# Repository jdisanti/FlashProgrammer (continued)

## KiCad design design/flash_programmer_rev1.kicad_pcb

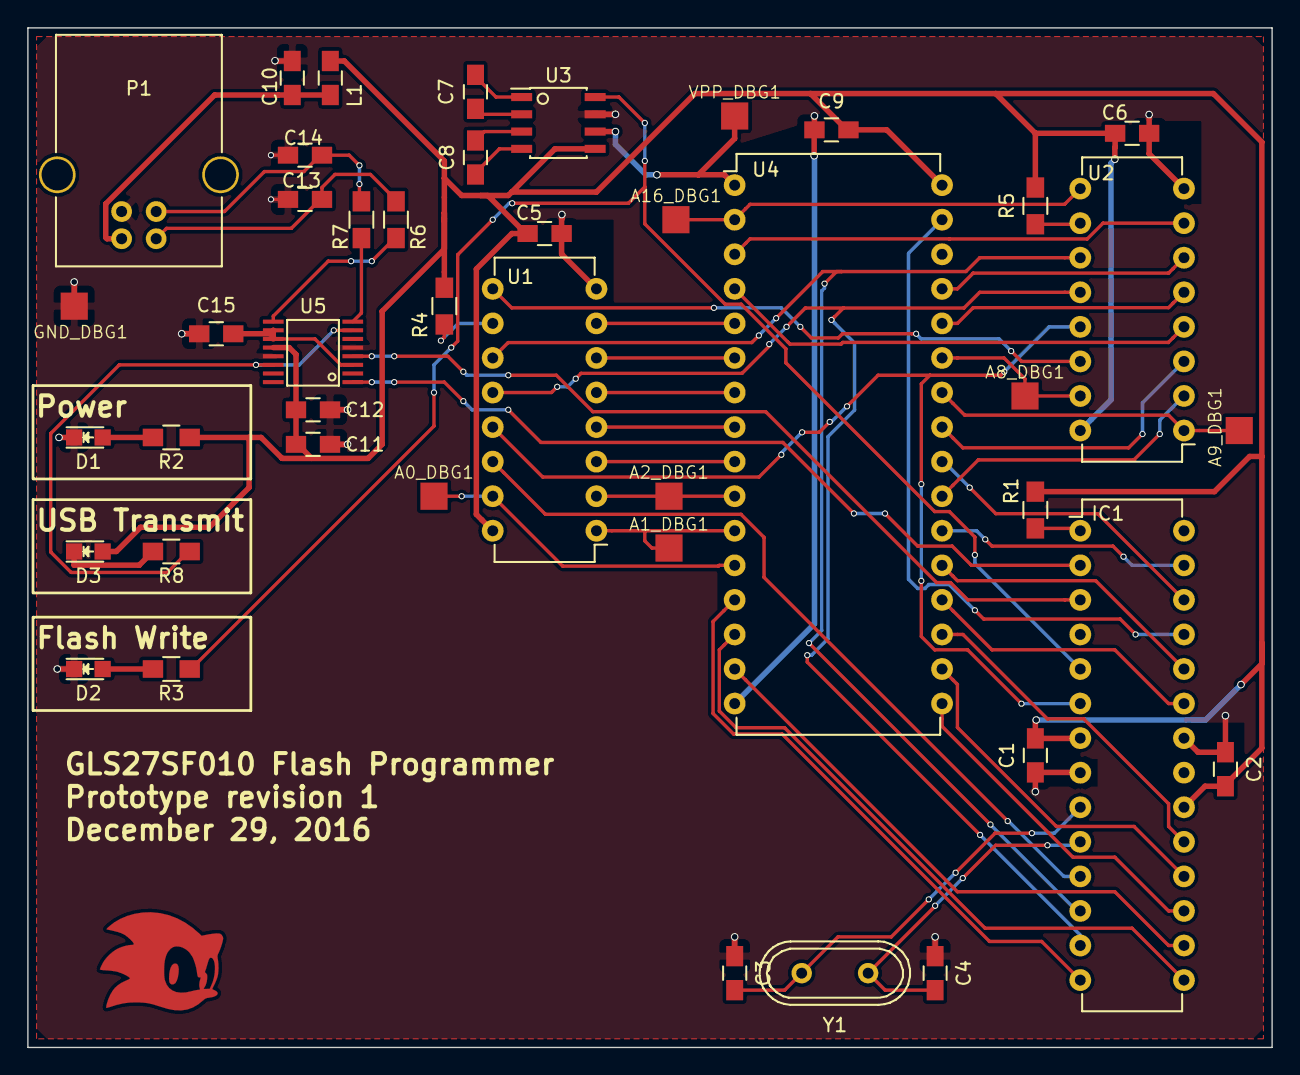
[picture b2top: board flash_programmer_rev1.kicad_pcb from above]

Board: 2 copper layers, 91.4 x 74.9 mm, 43 parts (0 on the bottom side), 58 nets.

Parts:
A0_DBG1, A1_DBG1, A2_DBG1, A8_DBG1, A9_DBG1, A16_DBG1: debug_pad; DBG_PAD
C1, C2, C5, C6, C9, C12, C15: 120nF; C_0805_HandSoldering
C3, C4: 22pF; C_0805_HandSoldering
C7, C8: 1uF; C_0805_HandSoldering
C10: 10nF; C_0805_HandSoldering
C11: 4.7uF; C_0805_HandSoldering
C13, C14: 47pF; C_0805_HandSoldering
D1, D2, D3: LED; LED_0805
GND_DBG1: debug_pad; DBG_PAD
IC1: ATMEGA328-P; DIP-28_W7.62mm
L1: Ferrite_Bead; C_0805_HandSoldering
P1: USB_B
R1, R4, R5: 10k; R_0805_HandSoldering
R2, R3, R8: 150; R_0805_HandSoldering
R6, R7: 27; R_0805_HandSoldering
U1, U2: 74HC595; DIP-16_W7.62mm
U3: MAX662A; SOIC-8_3.9x4.9mm_Pitch1.27mm
U4: GLS27SF010; DIP-32_W15.24mm
U5: FT230X; SSOP-16
VPP_DBG1: debug_pad; DBG_PAD
Y1: 16MHz; Crystal_HC49-U_Vertical

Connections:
/A0: A0_DBG1.1, U1.15, U4.12
/A1: A1_DBG1.1, U1.1, U4.11
/A2: A2_DBG1.1, U1.2, U4.10
/A3: U1.3, U4.9
/A4: U1.4, U4.8
/A5: U1.5, U4.7
/A6: U1.6, U4.6
/A7: U1.7, U4.5
/A8: A8_DBG1.1, U2.15, U4.27
/A9: A9_DBG1.1, U2.1, U4.26
/A10: U2.2, U4.23
/A11: U2.3, U4.25
/A12: U2.4, U4.4
/A13: U2.5, U4.28
/A14: U2.6, U4.29
/A15: U2.7, U4.3
/A16: A16_DBG1.1, U2.9, U4.2
/AOE: IC1.6, U1.13, U2.13
/CE#: IC1.27, U4.22
/D0: IC1.14, U4.13
/D1: IC1.15, U4.14
/D2: IC1.16, U4.15
/D3: IC1.17, U4.17
/D4: IC1.18, U4.18
/D5: IC1.19, U4.19
/D6: IC1.23, U4.20
/D7: IC1.24, U4.21
/Flash Programmer FTDI Circuit/USBDM: C13.1, P1.2, R6.2
/Flash Programmer FTDI Circuit/USBDP: C14.1, P1.3, R7.2
/Flash Programmer FTDI Circuit/VCCIO: C15.2, U5.3, U5.10, U5.11
/OE#: IC1.26, U4.24
/PGM#: IC1.25, U4.31
/RCK: IC1.13, U1.12, U2.12
/RXD: IC1.2, U5.1
/SCK: IC1.12, U1.11, U2.11
/SER: IC1.11, U1.14
/STU: IC1.5, R3.2, U3.8
/TXD: IC1.3, U5.4
/VPP: U3.6, U4.1, VPP_DBG1.1
GND: C1.1, C2.1, C3.1, C4.1, C5.1, C6.1, C9.1, C10.2, C11.2, C12.2, C13.2, C14.2, C15.1, D1.1, D2.1, GND_DBG1.1, IC1.8, IC1.22, P1.4, U1.8, U2.8, U3.7, U4.16, U5.5, U5.13
unnamed: C3.2, IC1.9, Y1.2
unnamed: C4.2, IC1.10, Y1.1
unnamed: C7.1, U3.1
unnamed: C7.2, U3.2
unnamed: C8.1, U3.4
unnamed: C8.2, U3.3
unnamed: C10.1, L1.2, P1.1
unnamed: D1.2, R2.1
unnamed: D2.2, R3.1
unnamed: D3.1, R8.1
unnamed: IC1.1, R1.2
unnamed: R4.1, U1.10
unnamed: R5.1, U2.10
unnamed: R6.1, U5.9
unnamed: R7.1, U5.8
unnamed: R8.2, U5.7, U5.14
unnamed: U1.9, U2.14
VCC: C1.2, C2.2, C5.2, C6.2, C9.2, C11.1, C12.1, D3.2, IC1.7, IC1.20, L1.1, R1.1, R2.2, R4.2, R5.2, U1.16, U2.16, U3.5, U4.32, U5.12

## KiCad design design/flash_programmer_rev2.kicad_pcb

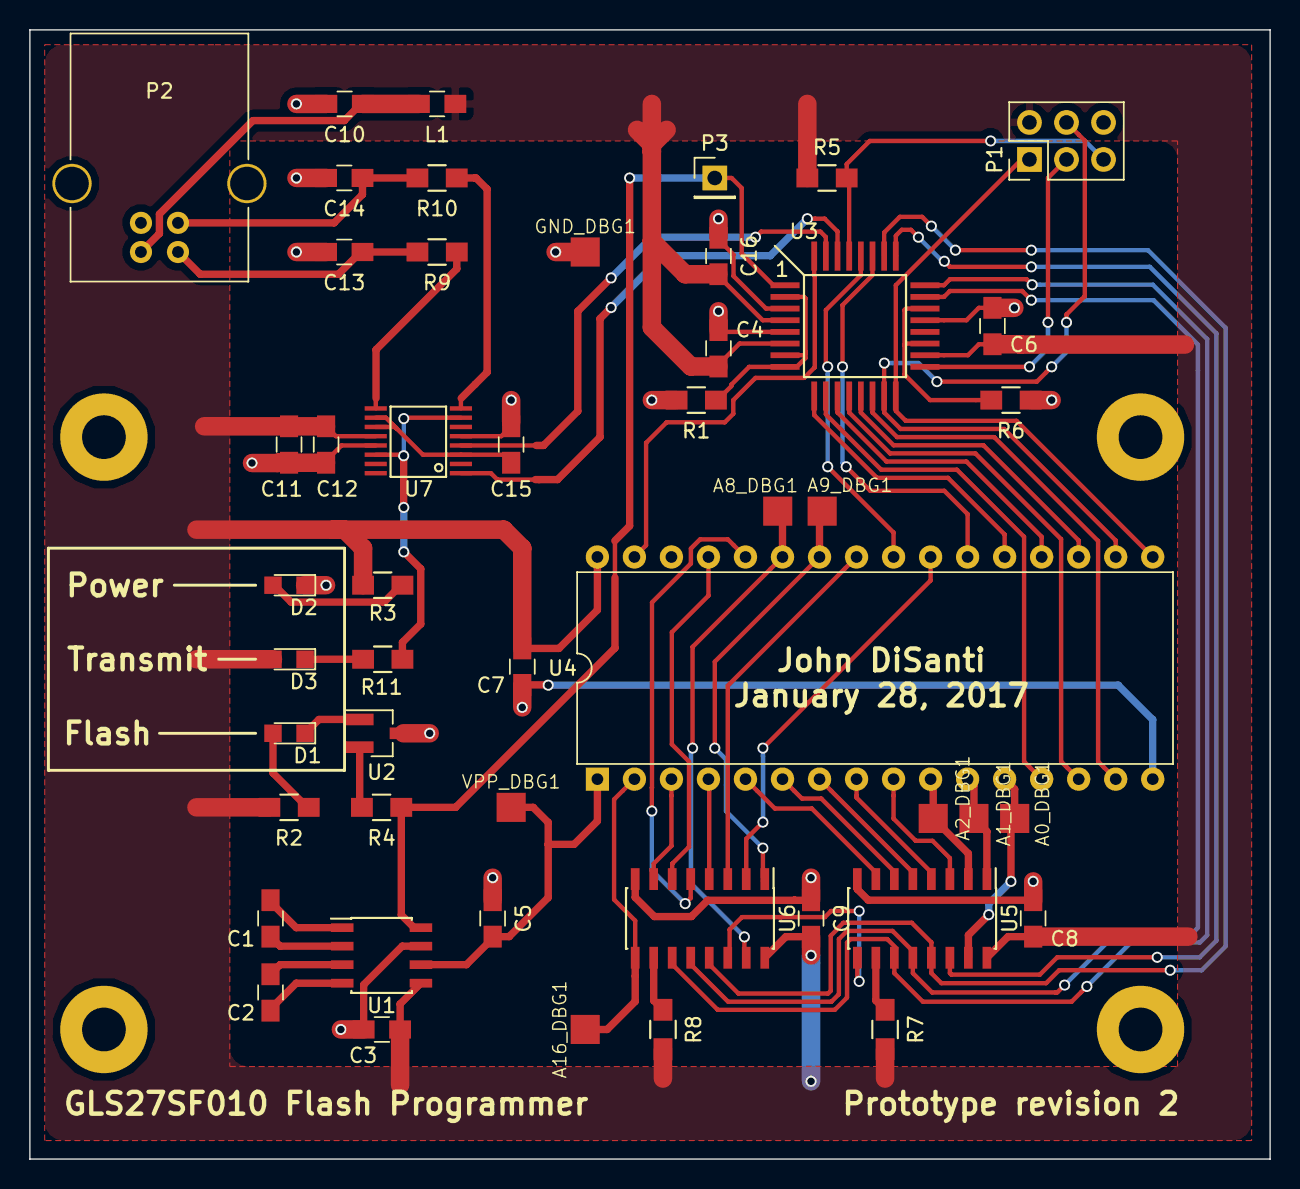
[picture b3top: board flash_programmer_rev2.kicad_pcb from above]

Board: 2 copper layers, 85.1 x 77.5 mm, 49 parts (0 on the bottom side), 61 nets.

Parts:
A0_DBG1, A1_DBG1, A2_DBG1, A8_DBG1, A9_DBG1, A16_DBG1: debug_pad; DBG_PAD
C1, C2: 22nF; C_0805_HandSoldering
C3, C5, C11: 4.7uF; C_0805_HandSoldering
C4, C6, C7, C8, C9, C12, C15, C16: 120nF; C_0805_HandSoldering
C10: 10nF; C_0805_HandSoldering
C13, C14: 47pF; C_0805_HandSoldering
D1, D2, D3: LED; LED_0805
GND_DBG1: debug_pad; DBG_PAD
L1: Ferrite_Bead; C_0805_HandSoldering
P1: ISP; Pin_Header_Straight_2x03_Pitch2.54mm
P2: USB_B
P3: STU_DBG1; Pin_Header_Straight_1x01_Pitch2.54mm
R1, R4, R5, R6, R7, R8: 10k; R_0805_HandSoldering
R2, R3, R11: 150; R_0805_HandSoldering
R9, R10: 27; R_0805_HandSoldering
U1: MAX662A; SOIC-8_3.9x4.9mm_Pitch1.27mm
U2: 2N3906; SOT-23_Handsoldering
U3: ATMEGA328P_TQFN; TQFP-32
U4: GLS27SF010; DIP-32_W15.24mm
U5, U6: 74HC595; SOIC-16_3.9x9.9mm_Pitch1.27mm
U7: FT230X; SSOP-16
VPP_DBG1: debug_pad; DBG_PAD

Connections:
/A0: A0_DBG1.1, U4.12, U5.15
/A1: A1_DBG1.1, U4.11, U5.1
/A2: A2_DBG1.1, U4.10, U5.2
/A3: U4.9, U5.3
/A4: U4.8, U5.4
/A5: U4.7, U5.5
/A6: U4.6, U5.6
/A7: U4.5, U5.7
/A8: A8_DBG1.1, U4.27, U6.15
/A9: A9_DBG1.1, U4.26, U6.1
/A10: U4.23, U6.2
/A11: U4.25, U6.3
/A12: U4.4, U6.4
/A13: U4.28, U6.5
/A14: U4.29, U6.6
/A15: U4.3, U6.7
/A16: A16_DBG1.1, U4.2, U6.9
/AOE: U3.26, U5.13, U6.13
/CE#: U3.27, U4.22
/D0: U3.10, U4.13
/D1: U3.12, U4.14
/D2: U3.14, U4.15
/D3: P1.1, U3.16, U4.17
/D4: P1.4, U3.15, U4.18
/D5: U3.13, U4.19
/D6: U3.11, U4.20
/D7: U3.9, U4.21
/Flash Programmer FTDI Circuit/USBDM: C13.1, P2.2, R9.2
/Flash Programmer FTDI Circuit/USBDP: C14.1, P2.3, R10.2
/Flash Programmer FTDI Circuit/VCCIO: C15.2, U7.3, U7.10, U7.11
/ISP_RST#: P1.5, R5.2, U3.29
/ISP_SCK: P1.3, U3.17
/OE#: U3.28, U4.24
/PGM#: U3.32, U4.31
/RCK: U3.23, U5.12, U6.12
/RXD: U3.30, U7.1
/SCK: U3.24, U5.11, U6.11
/SER: U3.25, U5.14
/STU: P3.1, R4.1, U1.8, U3.1
/TXD: U3.31, U7.4
/VPP: C5.2, U1.6, U4.1, VPP_DBG1.1
GND: C3.1, C4.1, C5.1, C6.1, C7.1, C8.1, C9.1, C10.2, C11.2, C12.2, C13.2, C14.2, C15.1, C16.1, D2.1, GND_DBG1.1, P1.6, P2.4, P2.5, R1.2, R6.1, U1.7, U2.3, U3.3, U3.5, U3.21, U4.16, U5.8, U6.8, U7.5, U7.13
unnamed: C1.1, U1.1
unnamed: C1.2, U1.2
unnamed: C2.1, U1.4
unnamed: C2.2, U1.3
unnamed: C10.1, L1.2, P2.1
unnamed: D1.1, U2.1
unnamed: D1.2, R2.1
unnamed: D2.2, R3.1
unnamed: D3.1, R11.1
unnamed: R1.1, U3.2, U3.7, U3.8
unnamed: R4.2, U2.2
unnamed: R6.2, U3.19, U3.22
unnamed: R7.1, U5.10
unnamed: R8.1, U6.10
unnamed: R9.1, U7.9
unnamed: R10.1, U7.8
unnamed: R11.2, U7.7, U7.14
unnamed: U5.9, U6.14
VCC: C3.2, C4.2, C6.2, C7.2, C8.2, C9.2, C11.1, C12.1, C16.2, D3.2, L1.1, P1.2, R2.2, R3.2, R5.1, R7.2, R8.2, U1.5, U3.4, U3.6, U3.18, U4.32, U5.16, U6.16, U7.12

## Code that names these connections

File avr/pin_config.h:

//
// 128K 17-bit Addressed 32-pin Flash ROM Programmer
// Copyright 2017 John DiSanti
//
// Copyright and related rights are licensed under the Solderpad Hardware License, Version 0.51 (the "License");
// you may not use this file except in compliance with the License. You may obtain a copy of the License at
// http://solderpad.org/licenses/SHL-0.51. Unless required by applicable law or agreed to in writing, software,
// hardware and materials distributed under this License is distributed on an "AS IS" BASIS, WITHOUT WARRANTIES
// OR CONDITIONS OF ANY KIND, either express or implied. See the License for the specific language governing
// permissions and limitations under the License.
//

#ifndef PIN_CONFIG_H_
#define PIN_CONFIG_H_

/* Pin manipulation macros */

#define _SET(type, name, bit)           type ## name  |= _BV(bit)
#define _CLEAR(type, name, bit)         type ## name  &= ~ _BV(bit)
#define _TOGGLE(type, name, bit)        type ## name  ^= _BV(bit)
#define _GET(type, name, bit)           ((type ## name >> bit) &  1)
#define _PUT(type, name, bit, value)    type ## name = (type ## name & (~_BV(bit))) | ((1 & (uint8_t) (value)) << (bit))

#define INPUT     0
#define OUTPUT    1

#define SET_PIN_MODE(pin, mode)         _PUT(DDR, pin, mode)
#define SET_OUTPUT(pin)                 _SET(DDR, pin)
#define SET_INPUT(pin)                  _CLEAR(DDR, pin)
#define SET_PIN_HIGH(pin)               _SET(PORT, pin)
#define SET_PIN_LOW(pin)                _CLEAR(PORT, pin)
#define TOGGLE_PIN(pin)                 _TOGGLE(PORT, pin)
#define GET_PIN(pin)                    _GET(PIN, pin)
#define SET_PIN(pin, value)             _PUT(PORT, pin, value)
#define SET_PULLUP(pin)                 _SET(PORT, pin)
#define CLEAR_PULLUP(pin)               _CLEAR(PORT, pin)

/* Pin configs */

// Port B
#define PIN_D5                B,0
#define PIN_D4                B,1
#define PIN_D3                B,2
#define PIN_D6                B,3
#define PIN_D2                B,4
#define PIN_D7                B,5
#define PIN_D0                B,6
#define PIN_D1                B,7

// Port C
#define PIN_UNUSED_PC0        C,0
#define PIN_UNUSED_PC1        C,1
#define PIN_A_SCK             C,2
#define PIN_A_RCK             C,3
#define PIN_CE_L              C,4
#define PIN_OE_L              C,5
#define PIN_ISP_RST_L         C,6
#define PIN_UNUSED_PC7        C,7

// Port D
#define PIN_RXD               D,0
#define PIN_TXD               D,1
#define PIN_PGM_L             D,2
#define PIN_A_OE_L            D,3
#define PIN_A_SER             D,4
#define PIN_A16               D,5
#define PIN_VPP_12V_EN_L      D,6
#define PIN_A9_VPP_EN_L       D,7

void init_pins();
void data_output_mode();
void data_input_mode();
void set_address(uint32_t address);
void set_data(uint8_t data);

void reset_12v();
void set_12v_vpp();
void set_12v_vpp_a9();

#endif /* PIN_CONFIG_H_ */

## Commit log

2017-02-11 Fix pin numbers on 2n3906
    The Base and Emitter were swapped which caused error in PCB design and
    manufacture. Fixing them for the future.
2017-02-11 Fix errors in PCB design
    Fixed the pin order on the 2n3906 transistor for the flash indicator LED.
    Corrected positions of labels for C15 and R10.
2017-02-13 Write flash read capability
2017-03-10 Redo PCB: fix errors and shrink
2017-03-10 Revise the PCB
    Added a ground test point, and enlarged annular rings around vias.
2017-03-10 Revise the silkscreens on the PCB
2017-03-10 Fix flash writing
    Flash erase does not work. Turns out we need 12V on the A9 line (which the
    current revision does not have capability for).
2017-03-10 Redraw schematic for clarity
2017-03-10 Associate footprints and correct pin orders for transistors
2017-03-10 Work in progress: Come up with untested A9_P circuit
2017-03-10 Redo the A9_P circuit with a P-channel MOSFET to avoid voltage drop
2017-03-10 Work in progress: Add `12V capability to A9
2017-03-11 Bug fix and more schematic cleanup
    The A9_VPP circuit wouldn't work in all cases, so I completely redid it and
    it's simpler now.
    Also started splitting up the schematic into even more sheets, and sprinkled in
    some TODO comments.
2017-03-12 More schematic clean up
2017-03-13 Create PCB for latest schematic design
2017-03-26 Revise software for latest design
    Chip erase now works
2017-03-26 Improve read performance
2017-03-26 Rewrite read script as a proper command-line program
2017-03-26 Add checksum to read code
2017-03-26 Fix a bug that prevented reading the last block
2017-03-27 Fix most write issues
    The first byte of the ROM is still written incorrectly for some reason.
2017-03-30 Changes made while troubleshooting
2017-05-01 Don't enforce input file size for ROM write operation
2017-05-03 Revised fab layers for easier assembly reference
2017-05-03 Bug fixes for the microcontroller code
    - Fix (almost) infinite loop due to unsigned int
    - Wait longer for 12V assertion which seems to have
    fixed the first two bytes not getting written
    - Don't disable output on shift registers as that
    prevents the second register from ever having a value
2017-05-04 Increase propagation delay after setting address
2017-05-04 Improve progress display in CLI
2017-05-04 Clean up AVR code, add code documentation, and apply license
2017-05-05 Apply license to software and add README
2017-05-06 Cleaned up the code in software/
    Added comments, proper error handling, and generally tidied up the code
2017-05-06 Apply license to schematic files
2017-05-06 Correction: ATMEGA328P -> ATMEGA328-AU
2017-05-06 Add license and OSHW logo to PCB
2017-05-06 Add PDFs of schematic and PCB, and add BOM file
2017-05-06 Add more to the README
2017-05-07 Add image of the programmer to the README
2017-05-07 Add demo to README
